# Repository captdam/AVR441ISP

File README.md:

This branch is for reference only! OUTDATED!

A quick note here.

The first design used Tiny25 (the smallest and cheapest AVR in DIP package) in raw mode. There is no logic in the AVR, it did nothing but translate signal from UART (from PC) to SPI (to target), then translate signal from SPI (from target) to UART (to PC). In another word, the PC was resbonsible for handling the SPI protocol.

Tiny25 only has one USI interface and no UART interface. The UART communication between ISP and PC must be done in software, the SPI communication between the ISP and the traget must be done in semi-software style.

It first seems reasonable to use scheme. <del>PC is powerful enough to handle the protocol control, programming process does not require high speed. Atleast, this is true for hobby purpose.</del>

Then, there is the problem:

First, the speed.

According to the AVR SPI protocol, sending 1 data bytes requires 4 SPI byte transaction between the ISP and the target. Furturemore, because the PC handles the SPI protoocol, the PC needs to send 4 bytes to ISP before the actual SPI transaction between the ISP and the target; after the SPI transaction, the ISP replys the 4 bytes back to PC in UART.

In another word, 8 UART bytes for 1 data byte. SPI communication is fast, not a big issue; however, the UART is a big hit.

For most PC, 115200 BAUD is the maximum. If we use 1 start bit, 8 data bit and 1 stop bit, 1 margin bit (in case clock on ISP is too slow), that will be 10472 UART byte every second. 8 UART bytes for 1 data byte, plus some waiting time for SPI communication and internal processing, that is 1000 data byte every second. Not mention the time for PC context switching when performing syscall (send UART, read UART).

During experiment, the throughput is less than 80 data byte every second.

Second, error rate.

At the beginning, server-client method is used. The client runs in web browser controls the display and the protocol, data to send and to receive is packed into HTTP request and send to a local server. The local server uses termios to access the UART interface. This method works without any issue, except it is not supportted on Windows. WSL can be used, but sometimes the server-side in WSL freezed.

To simplfy the process and elimilate the server side, Web serial API is used. Maybe this only applies to my PC, I some times lost receiver data. More specificly, I randomly lost the first byte in each 4-byte package.

The solution:

Raw mode is no longer an optimized solution. The PC should pack multiple data bytes into a packet to ISP. The ISP then decode the packet, perform error checking of the packet, then send the decoded data to target.

This method should increase data density, from 1/8 in raw mode, to X/X+N where X is packet layload and N is header length. This method should also decrease error rate, since less packet will be sent.

Tiny25 is also abandoned. Another chip, the Tiny441/841 provides 2 hardware UART interface and one SPI interface. It allows faster processing, higher reliability than software UART/SPI, and less strict timing. This chip is not in DIP, but SOP package can be used.

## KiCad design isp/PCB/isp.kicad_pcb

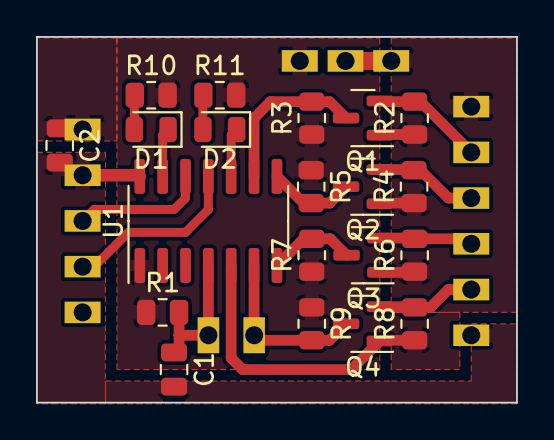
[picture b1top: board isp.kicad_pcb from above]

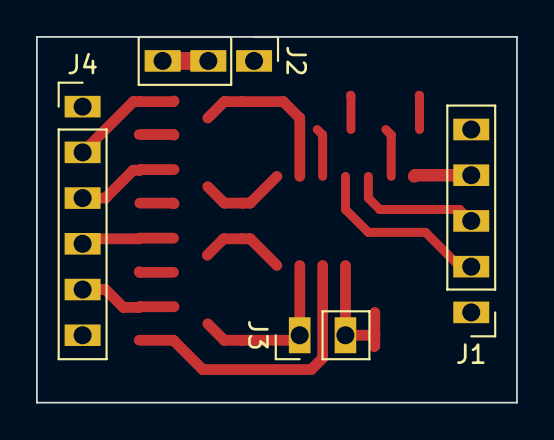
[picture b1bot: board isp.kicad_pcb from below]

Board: 2 copper layers, 26.7 x 20.3 mm, 24 parts (4 on the bottom side), 18 nets.

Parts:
C1, C2: 100n; C_0805_2012Metric
D1, D2: LED; LED_0805_2012Metric
J1: PC; PinHeader_1x05_P2.54mm_Vertical
J2: POW_SEL; PinHeader_1x03_P2.54mm_Vertical
J3: ISPRST; PinHeader_1x02_P2.54mm_Vertical
J4: ISP; PinHeader_1x06_P2.54mm_Vertical
Q1, Q2, Q3, Q4: 2N7002; SOT-23
R1, R2, R3, R4, R5, R6, R7, R8, R9, R10, R11: 10k; R_0805_2012Metric
U1: ATtiny841-SS; SOIC-14_3.9x8.7mm_P1.27mm

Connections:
+5V: C2.1, J1.5, J2.1, R1.1, R3.1, R5.1, R7.1, R9.1, R10.2, R11.2, U1.1 (VCC)
GND: C1.2, C2.2, J1.4, J4.6, U1.14 (GND)
MISO/Tx: Q2.3 (D), R5.2, U1.8 (PA5)
MOSI/Xck: Q3.3 (D), R7.2, U1.7 (PA6)
unnamed: D1.2 (A), R10.1
unnamed: D1.1 (K), U1.13 (AREF/PA0)
unnamed: D2.2 (A), R11.1
unnamed: D2.1 (K), U1.10 (PA3)
unnamed: C1.1, J3.2, R1.2, U1.4 (~RESET/PB3)
unnamed: J4.2, Q1.2 (S), R2.2
unnamed: J4.3, Q2.2 (S), R4.2
unnamed: J4.4, Q3.2 (S), R6.2
unnamed: J4.5, Q4.2 (S), R8.2
RST: J3.1, Q4.3 (D), R9.2, U1.6 (PA7)
Rx: J1.2, U1.11 (PA2)
SCK/Rx: Q1.3 (D), R3.2, U1.9 (PA4)
Tx: J1.3, U1.12 (PA1)
VCC: J2.2, J2.3, J4.1, Q1.1 (G), Q2.1 (G), Q3.1 (G), Q4.1 (G), R2.1, R4.1, R6.1, R8.1, U1.5 (PB2)

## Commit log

2023-11-29 Upload PCB and program
2023-12-03 Add webpage to http generator
2023-12-03 Add server program
2023-12-04 Server: change flow. Client: create ISP getters
2023-12-05 Optimize ISP circuit - Add ISP reset button and target enable SW - Change ISP output level shifter from NMOS to diode (save space & cost) - Rearrang PCB to save size, some SMD on back can overlap wit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
2023-12-05 Optimized doc image size
2023-12-09 Update PC server side: send 4 byte a time. AVR SPI cmd format is always 4 byte. For TPI (12bits), we can send 2 wors / 4 bytes, padding with idle bits
2023-12-09 Update ISP program. - Decrease SPI speed for stable communication. - Use internal pull-up for SPI input (change from circuit).
2023-12-09 Add client-side program
2023-12-09 Upload actual PCB and case photp and model file
2023-12-09 Cleanup
2023-12-13 Move HTTP related function into saperated files. Some design change, maybe I was too paranoid about reading HTML file from disk on-the-fly. Now, map web pages into memory when client request, unmap a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
2023-12-14 Working on GUI - GUI layout - Get Model (signature) - Get Fuse - Get Lock bits
2023-12-17 Add fuse/lock read/write function with check before write. Add new parts.
2023-12-18 Move AVR files to directory, add EEPROM functions
2023-12-20 ISP speed change: 9600 --> 115200 - Increase speed: Data stream (EEPROM/Flash) transfer at 9600BAUD is too slow (9600 only good for fuse). - Reduce resistor (50k --> 5k), Pull-up time too long for 50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
2024-01-22 Remove server side, use web SerialPort
2024-01-25 Add page write support, change part file structure
2024-02-29 New PCB design: Switch from tiny25 to tiny441/841
